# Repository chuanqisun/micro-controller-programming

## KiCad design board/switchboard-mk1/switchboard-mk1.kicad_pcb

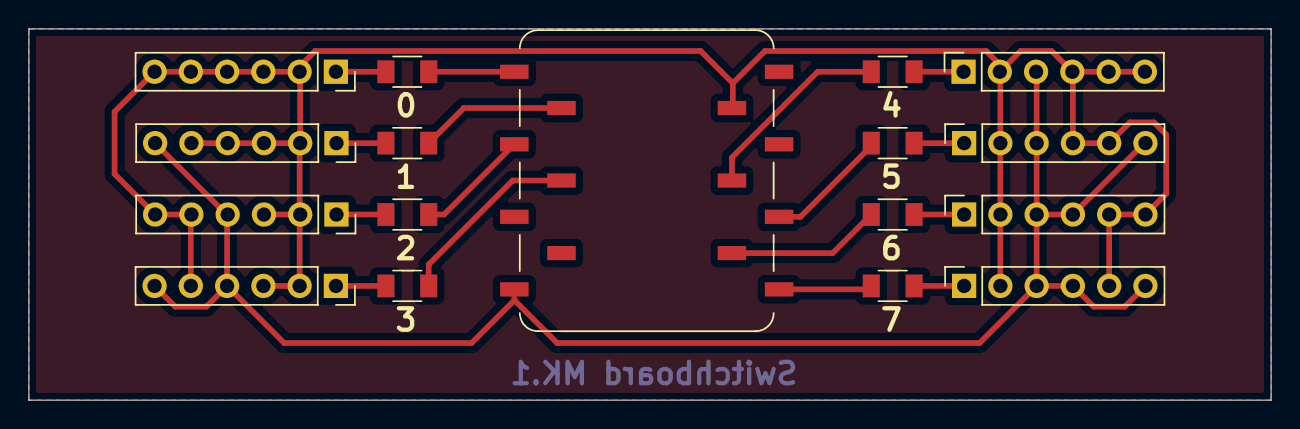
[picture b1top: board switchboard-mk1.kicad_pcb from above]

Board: 2 copper layers, 87.0 x 26.0 mm, 17 parts (0 on the bottom side), 18 nets.

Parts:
J1: Socket 02; PinSocket_1x06_P2.54mm_Vertical
J2: Socket 03; PinSocket_1x06_P2.54mm_Vertical
J3: Socket 01; PinSocket_1x06_P2.54mm_Vertical
J4: Socket 06; PinSocket_1x06_P2.54mm_Vertical
J5: Socket 05; PinSocket_1x06_P2.54mm_Vertical
J6: Socket 04; PinSocket_1x06_P2.54mm_Vertical
J7: Socket 07; PinSocket_1x06_P2.54mm_Vertical
J8: Socket 08; PinSocket_1x06_P2.54mm_Vertical
M1: XIAO ESP32-C3; Module_XIAO_Generic_SocketSMD
R1, R2, R7, R8, R9, R10, R11, R12: Resistor; R_1206

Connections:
GND: J1.2, J1.3, J1.4, J1.5, J2.2, J2.3, J2.5, J2.6, J3.2, J3.3, J3.4, J3.5, J3.6, J4.2, J4.4, J4.5, J5.2, J5.4, J5.5, J5.6, J6.2, J6.3, J6.5, J7.2, J7.5, J7.6, J8.2, J8.5, M1.13 (GND)
LED1: M1.1 (D0), R8.2
LED2: M1.2 (D1), R7.2
LED3: M1.3 (D2), R2.2
LED4: M1.4 (D3), R1.2
LED5: M1.11 (D10), R9.2
LED6: M1.10 (D9), R10.2
LED7: M1.9 (D8), R11.2
LED8: M1.8 (D7), R12.2
unnamed: J1.1, R7.1
unnamed: J2.1, R2.1
unnamed: J3.1, R8.1
unnamed: J4.1, R10.1
unnamed: J5.1, R9.1
unnamed: J6.1, R1.1
unnamed: J7.1, R11.1
unnamed: J8.1, R12.1
Pull up: J1.6, J2.4, J4.3, J4.6, J5.3, J6.4, J6.6, J7.3, J7.4, J8.3, J8.4, J8.6, M1.7 (D6)
